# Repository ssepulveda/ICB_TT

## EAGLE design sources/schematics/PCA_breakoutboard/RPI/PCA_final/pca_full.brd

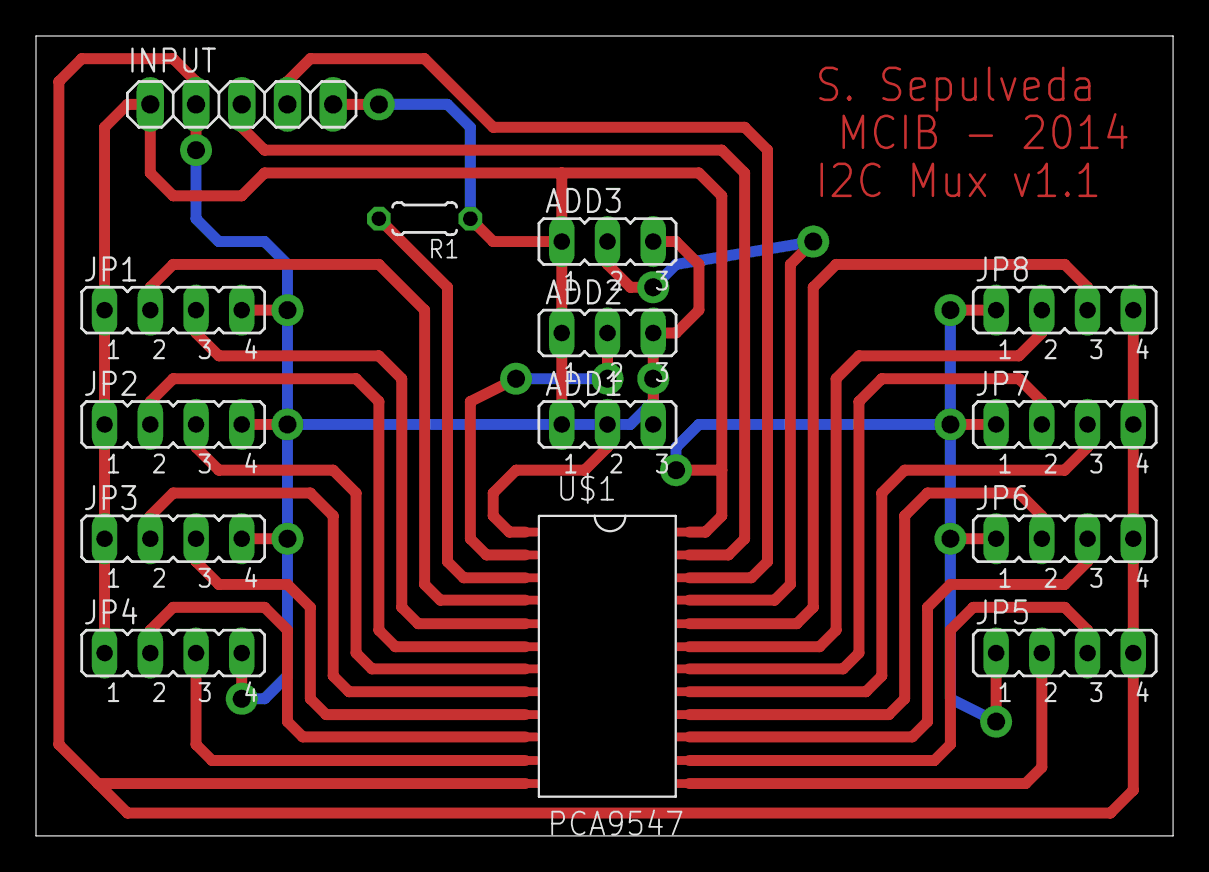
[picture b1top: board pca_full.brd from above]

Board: 2 copper layers, 63.2 x 44.4 mm, 14 parts (0 on the bottom side), 24 nets.

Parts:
ADD1, ADD2, ADD3: JP2
INPUT: 1X05
JP1, JP2, JP3, JP4, JP5, JP6, JP7, JP8: JP4
R1: 4k7; 0204/5
U$1: PCA9547; SO24

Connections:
+3V3: ADD1.1, ADD2.1, ADD3.1, INPUT.1, INPUT.5, JP1.1, JP2.1, JP3.1, JP4.1, JP5.1, JP6.1, JP7.1, JP8.1, R1.1, U$1.24
GND: ADD1.3, ADD2.3, ADD3.3, INPUT.2, JP1.4, JP2.4, JP3.4, JP4.4, JP5.4, JP6.4, JP7.4, JP8.4, U$1.12
unnamed: ADD1.2, U$1.1
unnamed: ADD2.2, U$1.2
unnamed: ADD3.2, U$1.21
unnamed: INPUT.4, U$1.22
unnamed: INPUT.3, U$1.23
unnamed: R1.2, U$1.3
SCL0: JP1.3, U$1.5
SCL1: JP2.3, U$1.7
SCL2: JP3.3, U$1.9
SCL3: JP4.3, U$1.11
SCL4: JP5.3, U$1.14
SCL5: JP6.3, U$1.15
SCL6: JP7.3, U$1.17
SCL7: JP8.3, U$1.20
SDA0: JP1.2, U$1.4
SDA1: JP2.2, U$1.6
SDA2: JP3.2, U$1.8
SDA3: JP4.2, U$1.10
SDA4: JP5.2, U$1.13
SDA5: JP6.2, U$1.16
SDA6: JP7.2, U$1.18
SDA7: JP8.2, U$1.19

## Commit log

2015-01-25 Updated Acknowledgements
